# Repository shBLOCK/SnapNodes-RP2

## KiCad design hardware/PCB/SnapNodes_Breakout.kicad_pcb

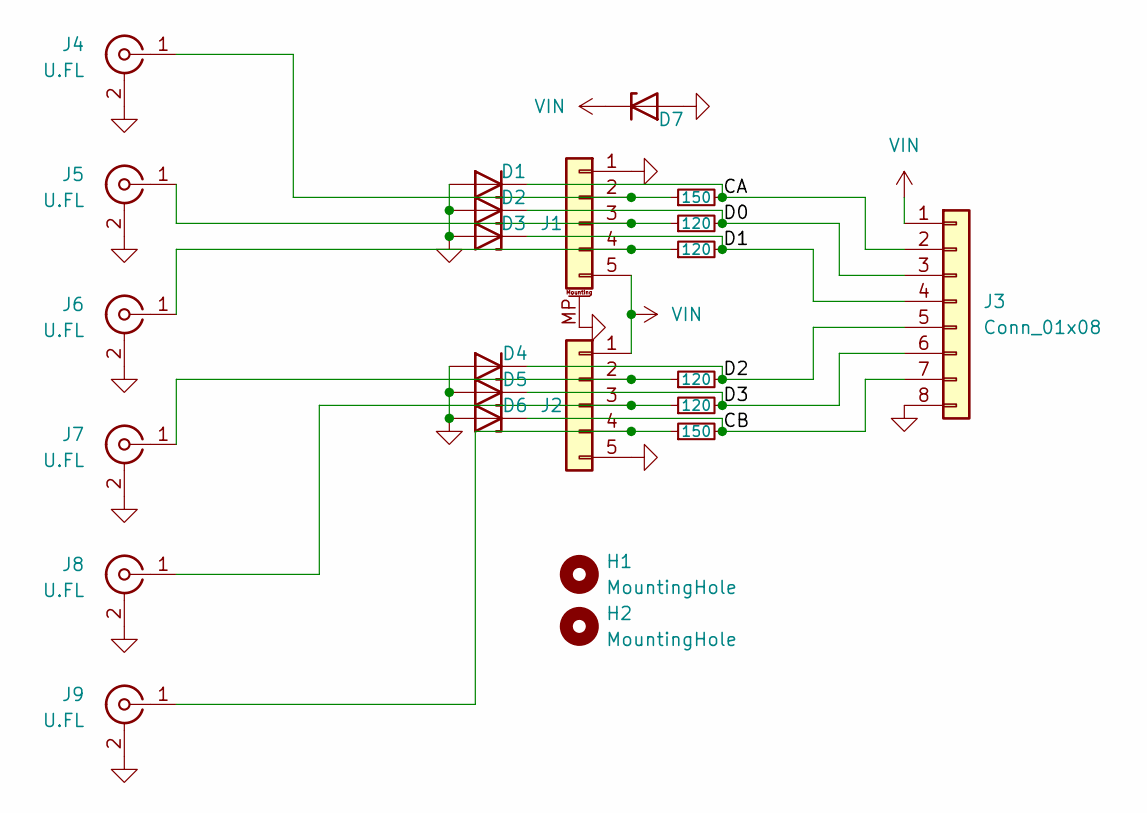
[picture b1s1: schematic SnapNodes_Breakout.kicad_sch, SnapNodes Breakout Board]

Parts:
D1, D2, D3, D4, D5, D6: PESD3V3S1BA; D_SOD-523; LCSC P/N C46550846
D7: PESD5V0S1BA; D_SOD-523; LCSC P/N C314264
H1, H2: MountingHole; MountingHole_2.2mm_M2
J1: P_Male; BC-15-5P380
J2: P_Female; BC-20-5PD160
J3: Conn_01x08; PinHeader_1x08_P2.54mm_Vertical
J4, J5, J6, J7, J8, J9: U.FL; U.FL_Hirose_U.FL-R-SMT-1_Vertical
R1, R6: 150; R_0402_1005Metric; LCSC P/N C25082
R2, R3, R4, R5: 120; R_0402_1005Metric; LCSC P/N C25079

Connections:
/CA: D1.1 (K), J3.2, R1.2
/CB: D6.1 (K), J3.7, R6.2
/D0: D2.1 (K), J3.3, R2.2
/D1: D3.1 (K), J3.4, R3.2
/D2: D4.1 (K), J3.5, R4.2
/D3: D5.1 (K), J3.6, R5.2
GND: D1.2 (A), D2.2 (A), D3.2 (A), D4.2 (A), D5.2 (A), D6.2 (A), D7.2 (A), J1.1, J1.MP (MountPin), J2.5, J3.8, J4.2 (Ext), J5.2 (Ext), J6.2 (Ext), J7.2 (Ext), J8.2 (Ext), J9.2 (Ext)
unnamed: J1.2, J4.1 (In), R1.1
unnamed: J1.3, J5.1 (In), R2.1
unnamed: J1.4, J6.1 (In), R3.1
unnamed: J2.2, J7.1 (In), R4.1
unnamed: J2.3, J8.1 (In), R5.1
unnamed: J2.4, J9.1 (In), R6.1
VIN: D7.1 (K), J1.5, J2.1, J3.1

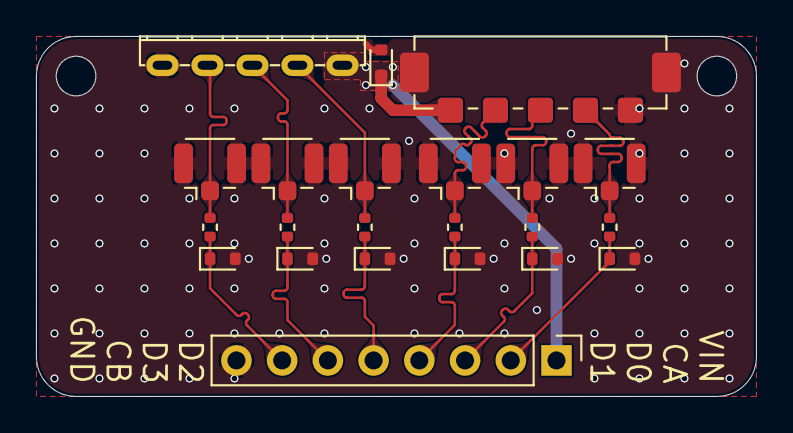
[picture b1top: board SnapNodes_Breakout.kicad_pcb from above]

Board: 4 copper layers, 40.0 x 20.0 mm, 24 parts (0 on the bottom side), 14 nets.

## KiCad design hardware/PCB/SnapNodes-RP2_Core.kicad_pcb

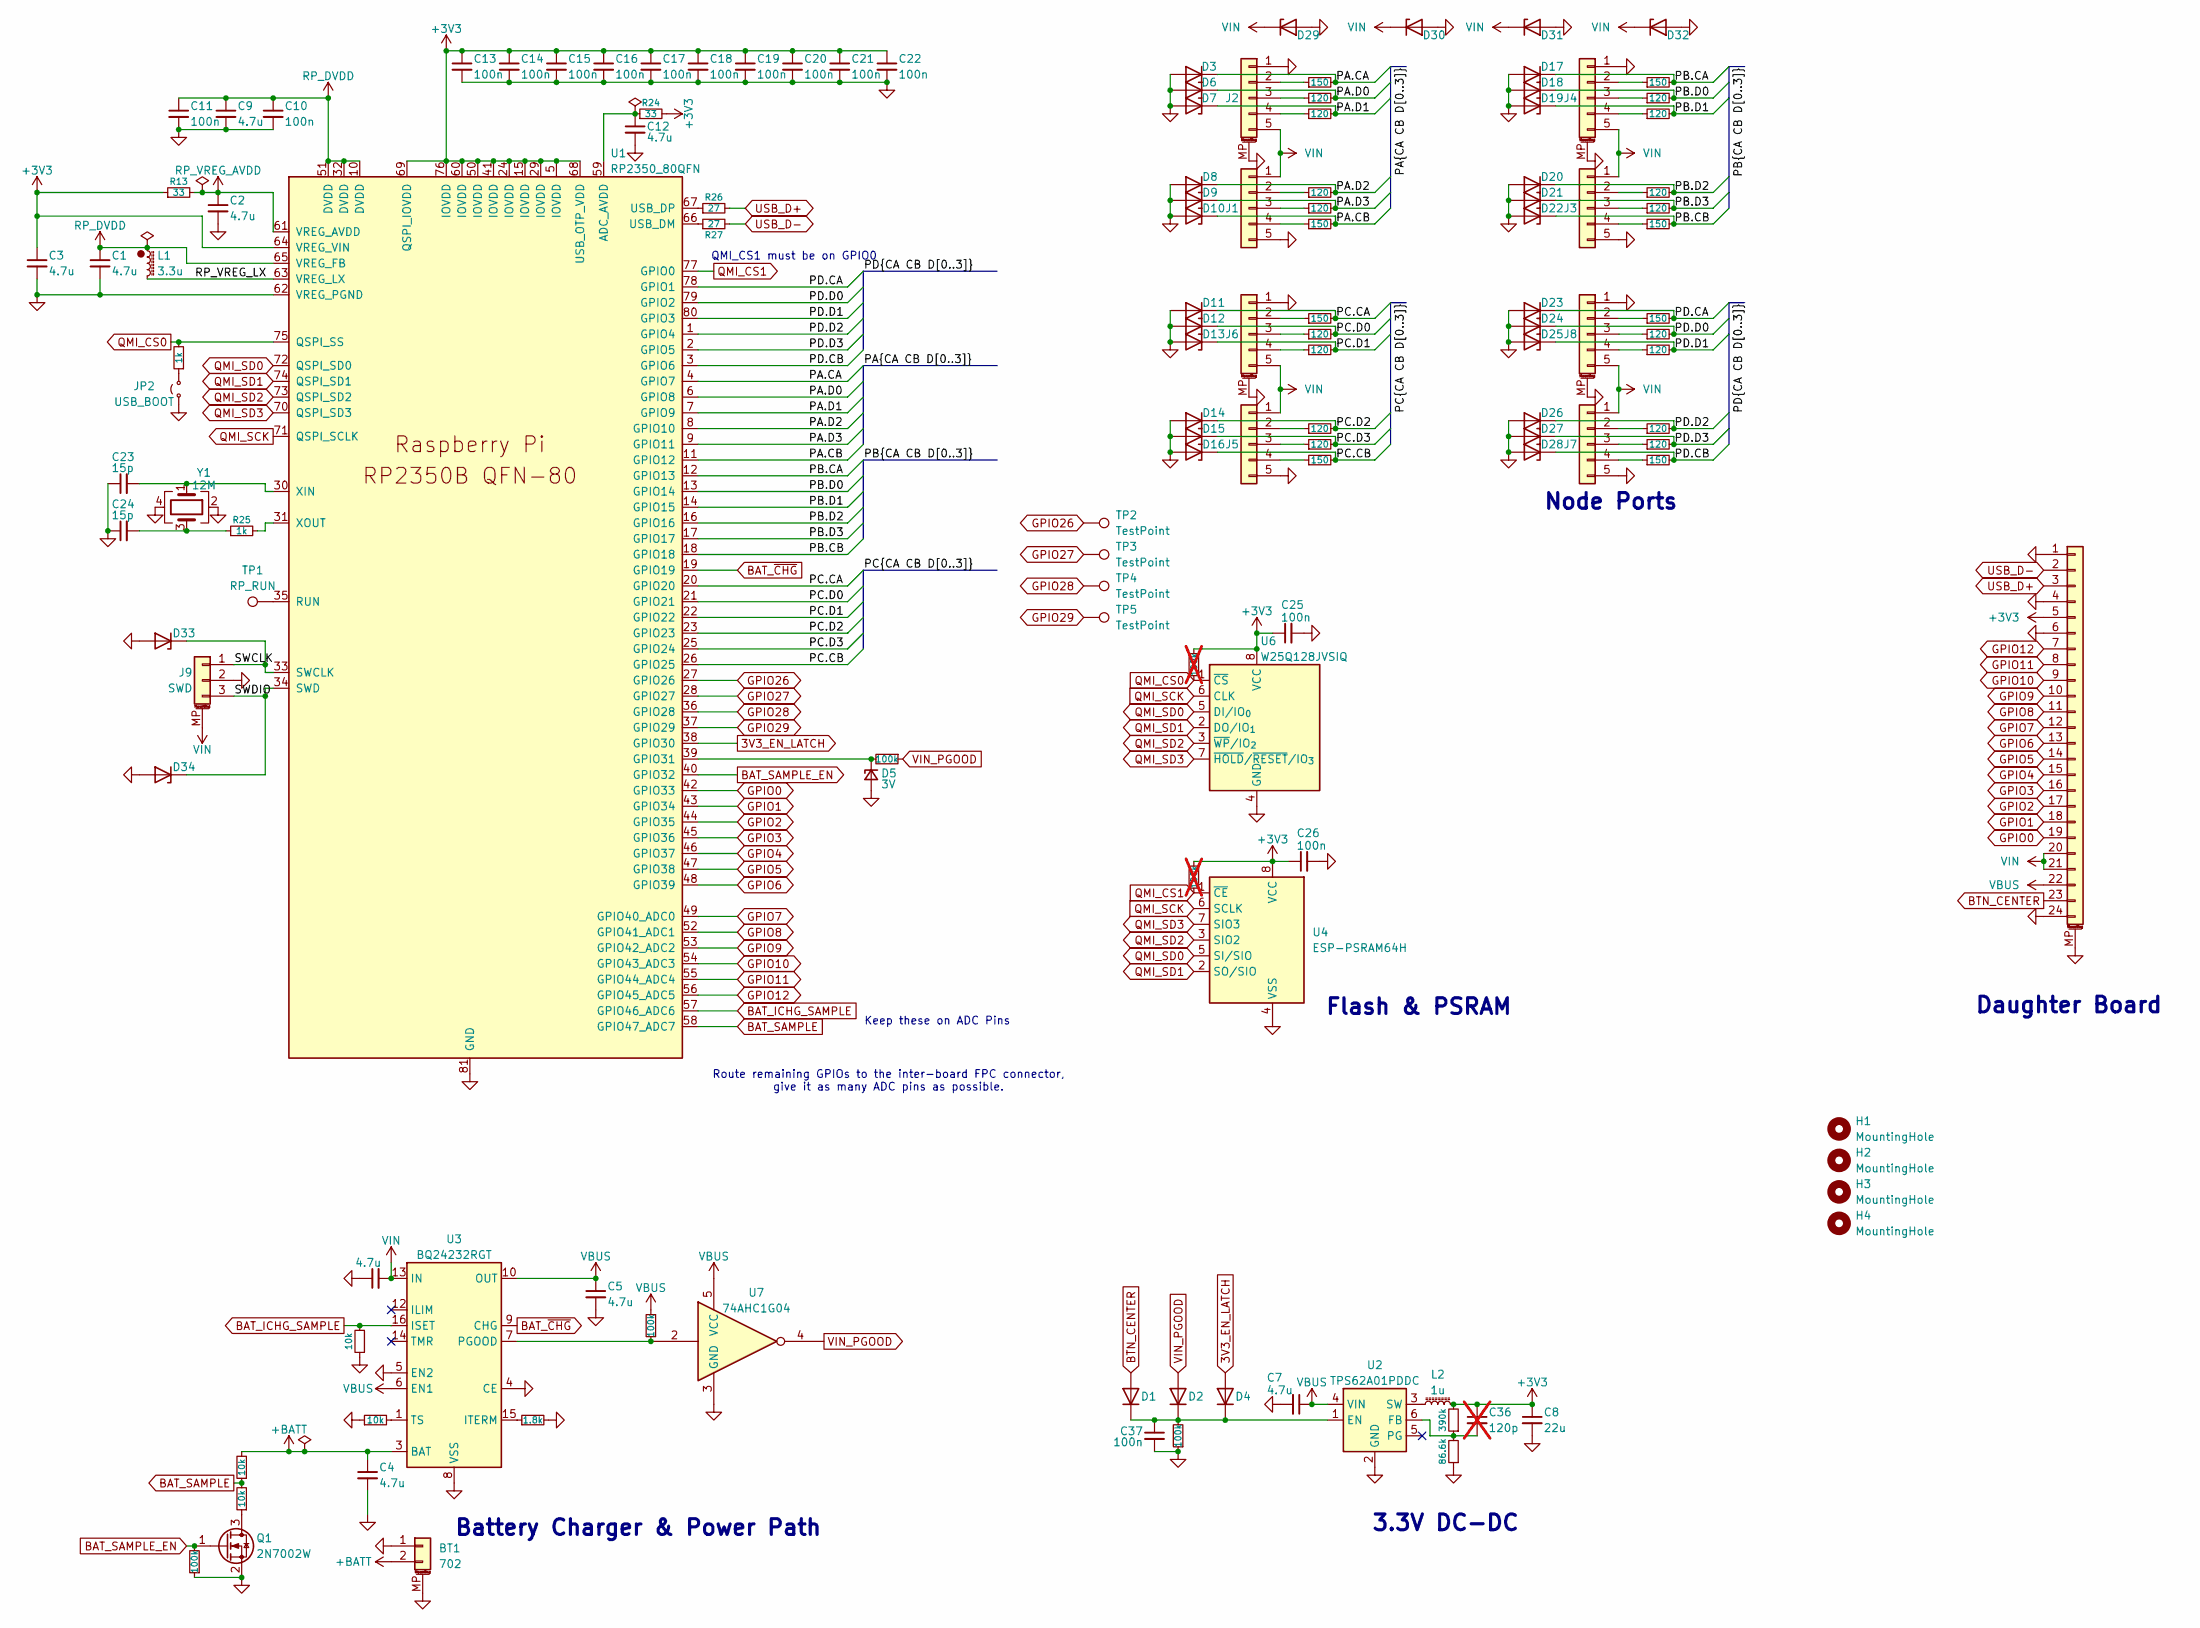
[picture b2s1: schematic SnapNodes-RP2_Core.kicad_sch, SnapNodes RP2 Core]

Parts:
BT1: 702; Molex_PicoBlade_53261-0271_1x02-1MP_P1.25mm_Horizontal; LCSC P/N C53477378
C1, C3: 4.7u; C_0402_1005Metric_small_pads; LCSC P/N C19666
C2, C4, C5, C6, C7, C9, C12: 4.7u; C_0402_1005Metric; LCSC P/N C19666
C8: 22u; C_0805_2012Metric; LCSC P/N C45783
C10, C11, C13, C14, C15, C16, C17, C18, C19, C20, C21, C22, C25, C26, C37: 100n; C_0402_1005Metric; LCSC P/N C1525
C23, C24: 15p; C_0402_1005Metric; LCSC P/N C1548
C36: 120p; C_0402_1005Metric; LCSC P/N C106996; not fitted
D1, D2, D4: 1N4148WT; D_SOD-523; LCSC P/N C7420320
D3, D6, D7, D8, D9, D10, D11, D12, D13, D14, D15, D16, D17, D18, D19, D20, D21, D22, D23, D24, D25, D26, D27, D28, D33, D34: PESD3V3S1BA; D_SOD-523; LCSC P/N C46550846
D5: 3V; D_SOD-523; LCSC P/N C2910134
D29, D30, D31, D32: PESD5V0S1BA; D_SOD-523; LCSC P/N C314264
H1, H2, H3, H4: MountingHole; MountingHole_2.2mm_M2
J1, J3, J5, J7: P_Female; BC-20-5PD160
J2, J4, J6, J8: P_Male; BC-15-5P380
J9: SWD; JST_SH_SM03B-SRSS-TB_1x03-1MP_P1.00mm_Horizontal; LCSC P/N C7430445
J20: Conn_01x24_MountingPin; FPC_Verticle_24pin_0.5mm; LCSC P/N C481246
JP2: USB_BOOT; PinHeader_1x02_P1.00mm_Vertical
L1: 3.3u; L_pol_2016; LCSC P/N C42411119
L2: 1u; L_Wuerth_MAPI-2010; LCSC P/N C7471163
Q1: 2N7002W; SOT-323_SC-70; LCSC P/N C7420322
R1, R4, R7, R10, R33, R37, R40, R43: 150; R_0402_1005Metric; LCSC P/N C25082
R2, R3, R5, R6, R8, R9, R11, R12, R31, R32, R35, R36, R38, R39, R41, R42: 120; R_0402_1005Metric; LCSC P/N C25079
R13, R24: 33; R_0402_1005Metric; LCSC P/N C25105
R14, R15, R17, R18: 10k; R_0402_1005Metric; LCSC P/N C25744
R16: 1.8k; R_0402_1005Metric; LCSC P/N C25871
R19, R22, R23, R34: 100k; R_0402_1005Metric; LCSC P/N C25741
R20: 86.6k; R_0402_1005Metric; LCSC P/N C19709
R21: 390k; R_0402_1005Metric; LCSC P/N C163467
R25, R30: 1k; R_0402_1005Metric; LCSC P/N C11702
R26, R27: 27; R_0402_1005Metric; LCSC P/N C25100
R28, R29: 100k; R_0402_1005Metric; LCSC P/N C25741; not fitted
TP1: RP_RUN; TestPoint_THTPad_D1.0mm_Drill0.5mm
TP2, TP3, TP4, TP5: TestPoint; TestPoint_Pad_D1.0mm
U1: RP2350_80QFN; RP2350-QFN-80-1EP_10x10_P0.4mm_EP3.4x3.4mm_ThermalVias; LCSC P/N C42415655
U2: TPS62A01PDDC; SOT-23-6; LCSC P/N C42267816
U3: BQ24232RGT; VQFN-16-1EP_3x3mm_P0.5mm_EP1.68x1.68mm_ThermalVias; LCSC P/N C528622
U4: ESP-PSRAM64H; SOIC-8_3.9x4.9mm_P1.27mm
U6: W25Q128JVSIQ; SOIC-8_5.3x5.3mm_P1.27mm; LCSC C113767
U7: 74AHC1G04; SOT-353_SC-70-5; LCSC P/N C52140422
Y1: 12M; Crystal_SMD_3225-4Pin_3.2x2.5mm; LCSC P/N C50430

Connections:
3V3_EN_LATCH: D4.2 (A), U1.38 (GPIO30)
+3V3: C3.1, C8.1, C13.1, C14.1, C15.1, C16.1, C17.1, C18.1, C19.1, C20.1, C21.1, C22.1, C25.1, C26.1, C36.1, J20.5, L2.2, R13.1, R21.2, R24.2, R28.2, R29.2, U1.5 (IOVDD), U1.15 (IOVDD), U1.24 (IOVDD), U1.29 (IOVDD), U1.41 (IOVDD), U1.50 (IOVDD), U1.60 (IOVDD), U1.64 (VREG_VIN), U1.68 (USB_OTP_VDD), U1.69 (QSPI_IOVDD), U1.76 (IOVDD), U4.8 (VCC), U6.8 (VCC)
+BATT: BT1.2, C4.1, R18.2, U3.2 (BAT), U3.3 (BAT)
/PA.CA: D3.1 (K), R1.2, U1.4 (GPIO7)
/PA.CB: D10.1 (K), R33.2, U1.11 (GPIO12)
/PA.D0: D6.1 (K), R31.2, U1.6 (GPIO8)
/PA.D1: D7.1 (K), R2.2, U1.7 (GPIO9)
/PA.D2: D8.1 (K), R32.2, U1.8 (GPIO10)
/PA.D3: D9.1 (K), R3.2, U1.9 (GPIO11)
/PB.CA: D17.1 (K), R4.2, U1.12 (GPIO13)
/PB.CB: D22.1 (K), R40.2, U1.18 (GPIO18)
/PB.D0: D18.1 (K), R38.2, U1.13 (GPIO14)
/PB.D1: D19.1 (K), R5.2, U1.14 (GPIO15)
/PB.D2: D20.1 (K), R39.2, U1.16 (GPIO16)
/PB.D3: D21.1 (K), R6.2, U1.17 (GPIO17)
/PC.CA: D11.1 (K), R7.2, U1.20 (GPIO20)
/PC.CB: D16.1 (K), R37.2, U1.26 (GPIO25)
/PC.D0: D12.1 (K), R35.2, U1.21 (GPIO21)
/PC.D1: D13.1 (K), R8.2, U1.22 (GPIO22)
/PC.D2: D14.1 (K), R36.2, U1.23 (GPIO23)
/PC.D3: D15.1 (K), R9.2, U1.25 (GPIO24)
/PD.CA: D23.1 (K), R10.2, U1.78 (GPIO1)
/PD.CB: D28.1 (K), R43.2, U1.3 (GPIO6)
/PD.D0: D24.1 (K), R41.2, U1.79 (GPIO2)
/PD.D1: D25.1 (K), R11.2, U1.80 (GPIO3)
/PD.D2: D26.1 (K), R42.2, U1.1 (GPIO4)
/PD.D3: D27.1 (K), R12.2, U1.2 (GPIO5)
/RP_VREG_LX: L1.2, U1.63 (VREG_LX)
/SWCLK: D33.1 (K), J9.1, U1.33 (SWCLK)
/SWDIO: D34.1 (K), J9.3, U1.34 (SWD)
BAT_ICHG_SAMPLE: R15.2, U1.57 (GPIO46_ADC6), U3.16 (ISET)
BAT_SAMPLE: R17.2, R18.1, U1.58 (GPIO47_ADC7)
BAT_SAMPLE_EN: Q1.1 (G), R19.2, U1.40 (GPIO32)
BAT_~CHG: U1.19 (GPIO19), U3.9 (CHG)
BTN_CENTER: D1.2 (A), J20.23
GND: BT1.1, BT1.MP (MountPin), C1.2, C2.2, C3.2, C4.2, C5.2, C6.1, C7.2, C8.2, C9.2, C10.2, C11.2, C12.2, C13.2, C14.2, C15.2, C16.2, C17.2, C18.2, C19.2, C20.2, C21.2, C22.2, C23.1, C24.1, C25.2, C26.2, C37.2, D3.2 (A), D5.2 (A), D6.2 (A), D7.2 (A), D8.2 (A), D9.2 (A), D10.2 (A), D11.2 (A), D12.2 (A), D13.2 (A), D14.2 (A), D15.2 (A), D16.2 (A), D17.2 (A), D18.2 (A), D19.2 (A), D20.2 (A), D21.2 (A), D22.2 (A), D23.2 (A), D24.2 (A), D25.2 (A), D26.2 (A), D27.2 (A), D28.2 (A), D29.2 (A), D30.2 (A), D31.2 (A), D32.2 (A), D33.2 (A), D34.2 (A), J1.5, J2.1, J2.MP (MountPin), J3.5, J4.1, J4.MP (MountPin), J5.5, J6.1, J6.MP (MountPin), J7.5, J8.1, J8.MP (MountPin), J9.2, J9.MP (MountPin), J20.1, J20.4, J20.6, J20.24, J20.MP (MountPin), JP2.1 (A), Q1.2 (S), R14.1, R15.1, R16.2, R19.1, R20.1, R34.1, U1.62 (VREG_PGND), U1.81 (GND), U2.2 (GND), U3.4 (CE), U3.5 (EN2), U3.8 (VSS), U3.17 (VSS), U4.4 (VSS), U6.4 (GND), U7.3 (GND), Y1.2, Y1.4
GPIO0: J20.19, U1.42 (GPIO33)
GPIO1: J20.18, U1.43 (GPIO34)
GPIO2: J20.17, U1.44 (GPIO35)
GPIO3: J20.16, U1.45 (GPIO36)
GPIO4: J20.15, U1.46 (GPIO37)
GPIO5: J20.14, U1.47 (GPIO38)
GPIO6: J20.13, U1.48 (GPIO39)
GPIO7: J20.12, U1.49 (GPIO40_ADC0)
GPIO8: J20.11, U1.52 (GPIO41_ADC1)
GPIO9: J20.10, U1.53 (GPIO42_ADC2)
GPIO10: J20.9, U1.54 (GPIO43_ADC3)
GPIO11: J20.8, U1.55 (GPIO44_ADC4)
GPIO12: J20.7, U1.56 (GPIO45_ADC5)
GPIO26: TP2.1 (1_1), U1.27 (GPIO26)
GPIO27: TP3.1 (1_1), U1.28 (GPIO27)
GPIO28: TP4.1 (1_1), U1.36 (GPIO28)
GPIO29: TP5.1 (1_1), U1.37 (GPIO29)
unnamed: C24.2, R25.1, Y1.3
unnamed: C37.1, D1.1 (K), D2.1 (K), D4.1 (K), R34.2, U2.1 (EN)
unnamed: D5.1 (K), R23.2, U1.39 (GPIO31)
unnamed: J1.2, R32.1
unnamed: J1.3, R3.1
unnamed: J1.4, R33.1
unnamed: J2.2, R1.1
unnamed: J2.3, R31.1
unnamed: J2.4, R2.1
unnamed: J3.2, R39.1
unnamed: J3.3, R6.1
unnamed: J3.4, R40.1
unnamed: J4.2, R4.1
unnamed: J4.3, R38.1
unnamed: J4.4, R5.1
unnamed: J5.2, R36.1
unnamed: J5.3, R9.1
unnamed: J5.4, R37.1
unnamed: J6.2, R7.1
unnamed: J6.3, R35.1
unnamed: J6.4, R8.1
unnamed: J7.2, R42.1
unnamed: J7.3, R12.1
unnamed: J7.4, R43.1
unnamed: J8.2, R10.1
unnamed: J8.3, R41.1
unnamed: J8.4, R11.1
unnamed: JP2.2 (B), R30.1
unnamed: Q1.3 (D), R17.1
unnamed: C12.1, R24.1, U1.59 (ADC_AVDD)
unnamed: TP1.1 (1_1), U1.35 (RUN)
unnamed: R27.1, U1.66 (USB_DM)
unnamed: R26.1, U1.67 (USB_DP)
unnamed: C23.2, U1.30 (XIN), Y1.1
unnamed: R25.2, U1.31 (XOUT)
unnamed: C36.2, R20.2, R21.1, U2.6 (FB)
unnamed: L2.1, U2.3 (SW)
unnamed: R16.1, U3.15 (ITERM)
unnamed: R22.2, U3.7 (PGOOD), U7.2
unnamed: R14.2, U3.1 (TS)
QMI_CS0: R28.1, R30.2, U1.75 (QSPI_SS), U6.1 (~CS)
QMI_CS1: R29.1, U1.77 (GPIO0), U4.1 (~CE)
QMI_SCK: U1.71 (QSPI_SCLK), U4.6 (SCLK), U6.6 (CLK)
QMI_SD0: U1.72 (QSPI_SD0), U4.5 (SI/SIO), U6.5 (DI/IO_{0})
QMI_SD1: U1.74 (QSPI_SD1), U4.2 (SO/SIO), U6.2 (DO/IO_{1})
QMI_SD2: U1.73 (QSPI_SD2), U4.3 (SIO2), U6.3 (~WP/IO_{2})
QMI_SD3: U1.70 (QSPI_SD3), U4.7 (SIO3), U6.7 (~HOLD/~RESET/IO_{3})
RP_DVDD: C1.1, C9.1, C10.1, C11.1, L1.1, U1.10 (DVDD), U1.32 (DVDD), U1.51 (DVDD), U1.65 (VREG_FB)
RP_VREG_AVDD: C2.1, R13.2, U1.61 (VREG_AVDD)
USB_D+: J20.3, R26.2
USB_D-: J20.2, R27.2
VBUS: C5.1, C7.1, J20.22, R22.1, U2.4 (VIN), U3.6 (EN1), U3.10 (OUT), U3.11 (OUT), U7.5 (VCC)
VIN: C6.2, D29.1 (K), D30.1 (K), D31.1 (K), D32.1 (K), J1.1, J2.5, J3.1, J4.5, J5.1, J6.5, J7.1, J8.5, J9.MP (MountPin), J20.20, J20.21, U3.13 (IN)
VIN_PGOOD: D2.2 (A), R23.1, U7.4

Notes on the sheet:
Battery Charger & Power Path
Route remaining GPIOs to the inter-board FPC connector, give it as many ADC pins as possible.
QMI_CS1 must be on GPIO0
Node Ports
Keep these on ADC Pins
Daughter Board
3.3V DC-DC
Flash & PSRAM

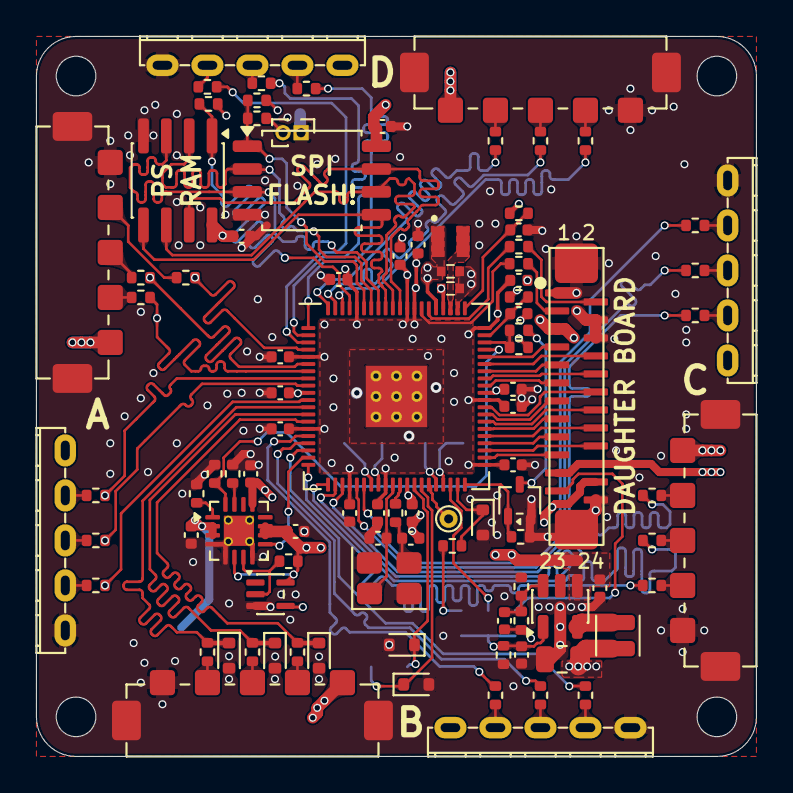
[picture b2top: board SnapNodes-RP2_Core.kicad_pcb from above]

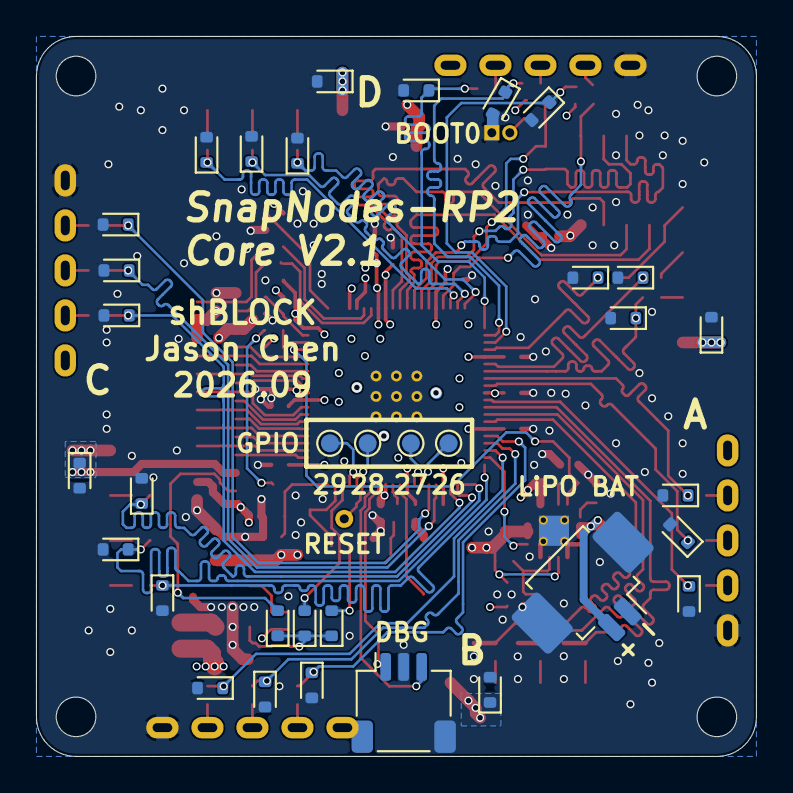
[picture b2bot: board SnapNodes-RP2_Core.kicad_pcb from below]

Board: 4 copper layers, 40.0 x 40.0 mm, 136 parts (34 on the bottom side), 107 nets.

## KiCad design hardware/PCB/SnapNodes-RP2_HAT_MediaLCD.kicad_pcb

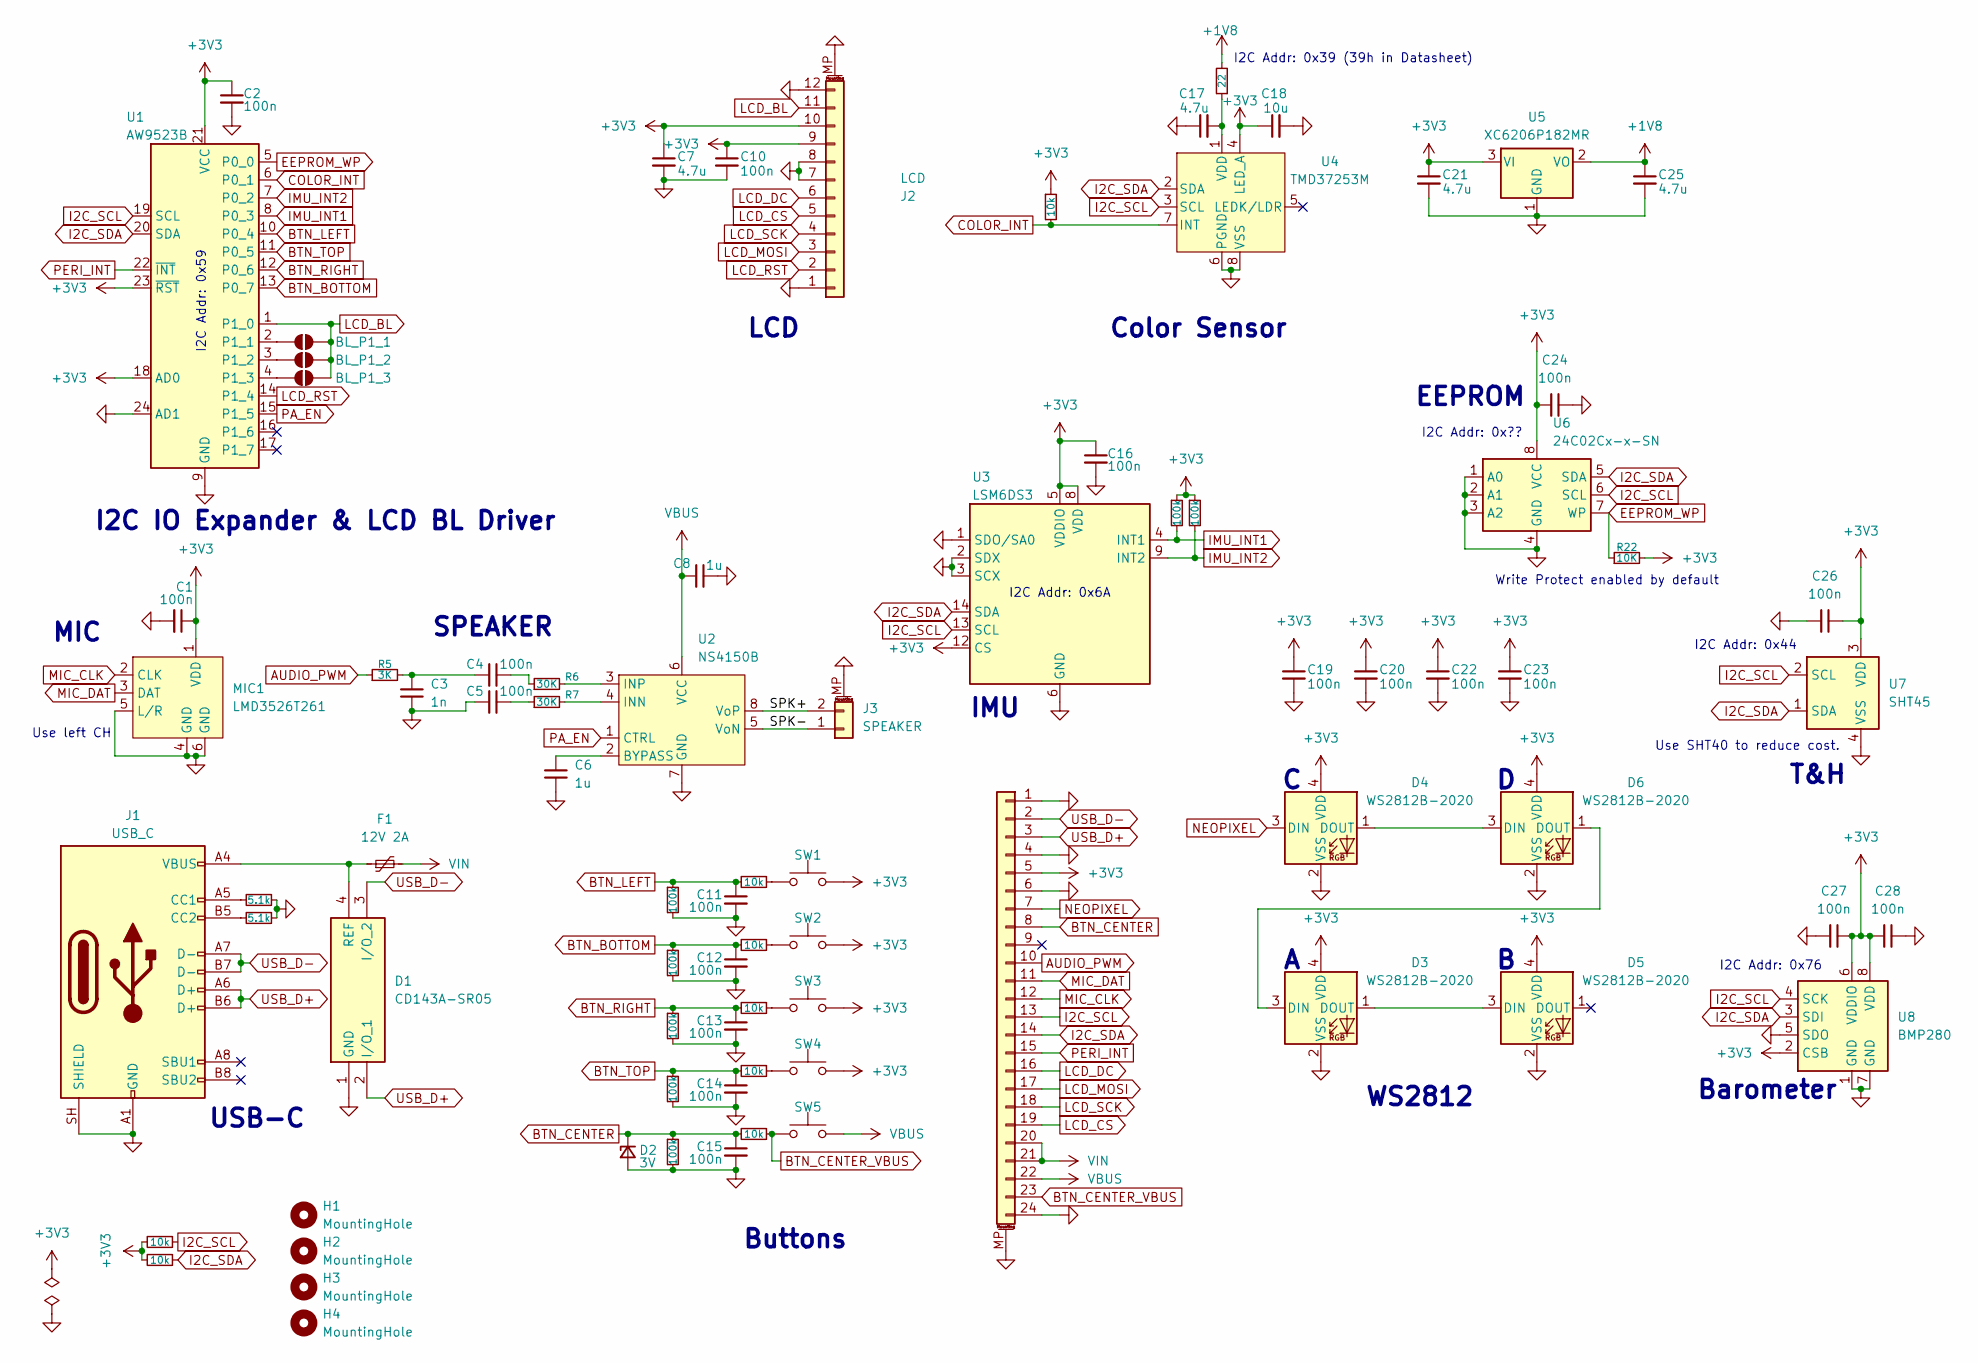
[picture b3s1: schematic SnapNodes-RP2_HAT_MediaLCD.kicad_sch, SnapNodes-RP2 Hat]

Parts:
C1, C2, C4, C5, C10, C11, C12, C13, C14, C15, C16, C19, C20, C22, C23, C24, C26, C27, C28: 100n; C_0603_1608Metric; LCSC P/N C14663
C3: 1n; C_0603_1608Metric; LCSC P/N C1588
C6, C8: 1u; C_0603_1608Metric; LCSC P/N C15849
C7, C17, C21, C25: 4.7u; C_0603_1608Metric; LCSC P/N C19666
C18: 10u; C_0603_1608Metric; LCSC P/N C19702
D1: CD143A-SR05; SOT-143; Manufacturer_Part_Number CD143A-SR05; Mouser Part Number 652-CD143A-SR05
D2: 3V; D_SOD-523; LCSC P/N C2910134
D3, D4, D5, D6: WS2812B-2020; LED_WS2812B-2020_PLCC4_2.0x2.0mm; LCSC P/N C52917434
F1: 12V 2A; Fuse_0805_2012Metric; LCSC P/N C48783161
H1, H2, H3, H4: MountingHole; MountingHole_2.2mm_M2
J1: USB_C; USB_C_Receptacle_GCT_USB4105-xx-A_16P_TopMnt_Horizontal; LCSC P/N C2765186
J2: LCD; TE_1-1734839-2_1x12-1MP_P0.5mm_Horizontal; LCSC P/N C49274051
J3: SPEAKER; Molex_PicoBlade_53261-0271_1x02-1MP_P1.25mm_Horizontal; LCSC P/N C53477378
J4: Conn_01x24_MountingPin; FPC_Verticle_24pin_0.5mm; LCSC P/N C481246
JP1: BL_P1_1; SolderJumper-2_P1.3mm_Open_RoundedPad1.0x1.5mm
JP2: BL_P1_2; SolderJumper-2_P1.3mm_Open_RoundedPad1.0x1.5mm
JP3: BL_P1_3; SolderJumper-2_P1.3mm_Open_RoundedPad1.0x1.5mm
MIC1: LMD3526T261; MIC-SMD_6P-L3.5-W2.7-P0.884-TR; LCSC P/N C49230436
R1, R2, R13, R14, R15, R16, R17, R18: 10k; R_0603_1608Metric; LCSC P/N C25804
R3, R4: 5.1k; R_0603_1608Metric; LCSC P/N C23186
R5: 3K; R_0603_1608Metric; LCSC P/N C4211
R6, R7: 30K; R_0603_1608Metric; LCSC P/N C22984
R8, R9, R10, R11, R12, R19, R20: 100k; R_0603_1608Metric; LCSC P/N C25803
R21: 22; R_0603_1608Metric; LCSC P/N C23345
R22: 10K; R_0603_1608Metric; LCSC P/N C25804
SW1: Left; SW_SPST_PTS647_Sx38
SW2: Bottom; SW_SPST_PTS647_Sx38
SW3: Right; SW_SPST_PTS647_Sx38
SW4: Top; SW_SPST_PTS647_Sx38
SW5: Center; SW_SPST_PTS647_Sx38
U1: AW9523B; QFN-24-1EP_4x4mm_P0.5mm_EP2.7x2.7mm_ThermalVias; LCSC P/N C148077
U2: NS4150B; MSOP-8_3x3mm_P0.65mm; LCSC P/N C189961
U3: LSM6DS3; LGA-14_3x2.5mm_P0.5mm_LayoutBorder3x4y; LCSC P/N C95230
U4: TMD37253M; LGA8_TMD37253_OSM; LCSC P/N C2153068
U5: XC6206P182MR; SOT-23-3; LCSC P/N C347373
U6: 24C02Cx-x-SN; SOIC-8_3.9x4.9mm_P1.27mm
U7: SHT45; Sensirion_DFN-4_1.5x1.5mm_P0.8mm_SHT4x_NoCentralPad
U8: BMP280; Bosch_LGA-8_2x2.5mm_P0.65mm_ClockwisePinNumbering

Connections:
+1V8: C25.1, R21.2, U5.2 (VO)
+3V3: C1.1, C2.1, C7.1, C10.1, C16.1, C18.1, C19.1, C20.1, C21.1, C22.1, C23.1, C24.1, C26.2, C27.2, C28.1, D3.4 (VDD), D4.4 (VDD), D5.4 (VDD), D6.4 (VDD), J2.9, J2.10, J4.5, MIC1.1 (VDD), R1.2, R2.2, R18.1, R19.1, R20.1, R22.2, SW1.2, SW2.2, SW3.2, SW4.2, U1.18 (AD0), U1.21 (VCC), U1.23 (~RST), U3.5 (VDDIO), U3.8 (VDD), U3.12 (CS), U4.4 (LED_A), U5.3 (VI), U6.8 (VCC), U7.3 (VDD), U8.2 (CSB), U8.6 (VDDIO), U8.8 (VDD)
/SPK+: J3.2, U2.8 (VoP)
/SPK-: J3.1, U2.5 (VoN)
AUDIO_PWM: J4.10, R5.1
BTN_BOTTOM: C12.1, R9.1, R14.2, U1.13 (P0_7)
BTN_CENTER: C15.1, D2.1 (K), J4.8, R12.1, R17.2
BTN_CENTER_VBUS: J4.23, R17.1, SW5.1
BTN_LEFT: C11.1, R8.1, R13.2, U1.10 (P0_4)
BTN_RIGHT: C13.1, R10.1, R15.2, U1.12 (P0_6)
BTN_TOP: C14.1, R11.1, R16.2, U1.11 (P0_5)
COLOR_INT: R18.2, U1.6 (P0_1), U4.7 (INT)
EEPROM_WP: R22.1, U1.5 (P0_0), U6.7 (WP)
GND: C1.2, C2.2, C3.1, C5.1, C6.1, C7.2, C8.1, C10.2, C11.2, C12.2, C13.2, C14.2, C15.2, C16.2, C17.1, C18.2, C19.2, C20.2, C21.2, C22.2, C23.2, C24.2, C25.2, C26.1, C27.1, C28.2, D1.1 (GND), D2.2 (A), D3.2 (VSS), D4.2 (VSS), D5.2 (VSS), D6.2 (VSS), J1.A1 (GND), J1.A12 (GND), J1.B1 (GND), J1.B12 (GND), J1.SH (SHIELD), J2.1, J2.7, J2.8, J2.12, J2.MP (MountPin), J3.MP (MountPin), J4.1, J4.4, J4.6, J4.24, J4.MP (MountPin), MIC1.4 (GND), MIC1.5 (L/R), MIC1.6 (GND), R3.1, R4.1, R8.2, R9.2, R10.2, R11.2, R12.2, U1.9 (GND), U1.24 (AD1), U1.25 (GND), U2.7 (GND), U3.1 (SDO/SA0), U3.2 (SDX), U3.3 (SCX), U3.6 (GND), U3.7 (GND), U4.6 (PGND), U4.8 (VSS), U5.1 (GND), U6.1 (A0), U6.2 (A1), U6.3 (A2), U6.4 (GND), U7.4 (VSS), U8.1 (GND), U8.5 (SDO), U8.7 (GND)
I2C_SCL: J4.13, R1.1, U1.19 (SCL), U3.13 (SCL), U4.3 (SCL), U6.6 (SCL), U7.2 (SCL), U8.4 (SCK)
I2C_SDA: J4.14, R2.1, U1.20 (SDA), U3.14 (SDA), U4.2 (SDA), U6.5 (SDA), U7.1 (SDA), U8.3 (SDI)
IMU_INT1: R19.2, U1.8 (P0_3), U3.4 (INT1)
IMU_INT2: R20.2, U1.7 (P0_2), U3.9 (INT2)
LCD_BL: J2.11, JP1.2 (B), JP2.2 (B), JP3.2 (B), U1.1 (P1_0)
LCD_CS: J2.5, J4.19
LCD_DC: J2.6, J4.16
LCD_MOSI: J2.3, J4.17
LCD_RST: J2.2, U1.14 (P1_4)
LCD_SCK: J2.4, J4.18
MIC_CLK: J4.12, MIC1.2 (CLK)
MIC_DAT: J4.11, MIC1.3 (DAT)
NEOPIXEL: D4.3 (DIN), J4.7
unnamed: C3.2, C4.1, R5.2
unnamed: C4.2, R6.1
unnamed: C5.2, R7.1
unnamed: D1.4 (REF), F1.1, J1.A4 (VBUS), J1.A9 (VBUS), J1.B4 (VBUS), J1.B9 (VBUS)
unnamed: D3.3 (DIN), D6.1 (DOUT)
unnamed: D3.1 (DOUT), D5.3 (DIN)
unnamed: D4.1 (DOUT), D6.3 (DIN)
unnamed: J1.A5 (CC1), R3.2
unnamed: J1.B5 (CC2), R4.2
unnamed: JP1.1 (A), U1.2 (P1_1)
unnamed: JP2.1 (A), U1.3 (P1_2)
unnamed: JP3.1 (A), U1.4 (P1_3)
unnamed: R13.1, SW1.1
unnamed: R14.1, SW2.1
unnamed: R15.1, SW3.1
unnamed: R16.1, SW4.1
unnamed: C6.2, U2.2 (BYPASS)
unnamed: R7.2, U2.4 (INN)
unnamed: R6.2, U2.3 (INP)
unnamed: C17.2, R21.1, U4.1 (VDD)
PA_EN: U1.15 (P1_5), U2.1 (CTRL)
PERI_INT: J4.15, U1.22 (~INT)
USB_D+: D1.2 (I/O_1), J1.A6 (D+), J1.B6 (D+), J4.3
USB_D-: D1.3 (I/O_2), J1.A7 (D-), J1.B7 (D-), J4.2
VBUS: C8.2, J4.22, SW5.2, U2.6 (VCC)
VIN: F1.2, J4.20, J4.21

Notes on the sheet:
I2C IO Expander & LCD BL Driver
Barometer
SPEAKER
Color Sensor
USB-C
EEPROM
I2C Addr: 0x76
WS2812
Use left CH
MIC
Buttons
LCD
I2C Addr: 0x44
I2C Addr: 0x59
I2C Addr: 0x39 (39h in Datasheet)
I2C Addr: 0x6A
IMU
I2C Addr: 0x??
Use SHT40 to reduce cost.
Write Protect enabled by default
T&H

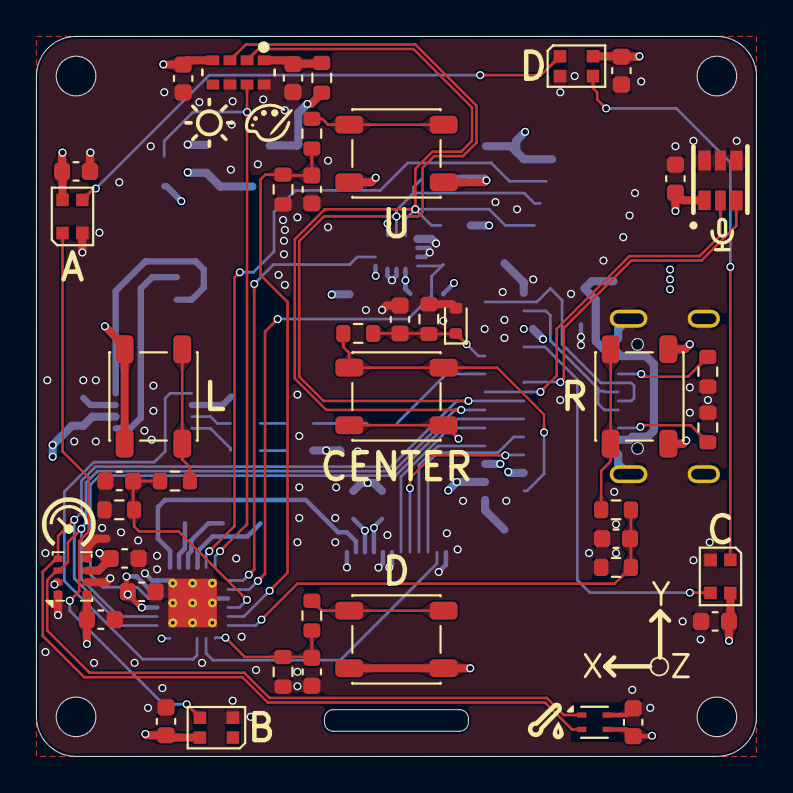
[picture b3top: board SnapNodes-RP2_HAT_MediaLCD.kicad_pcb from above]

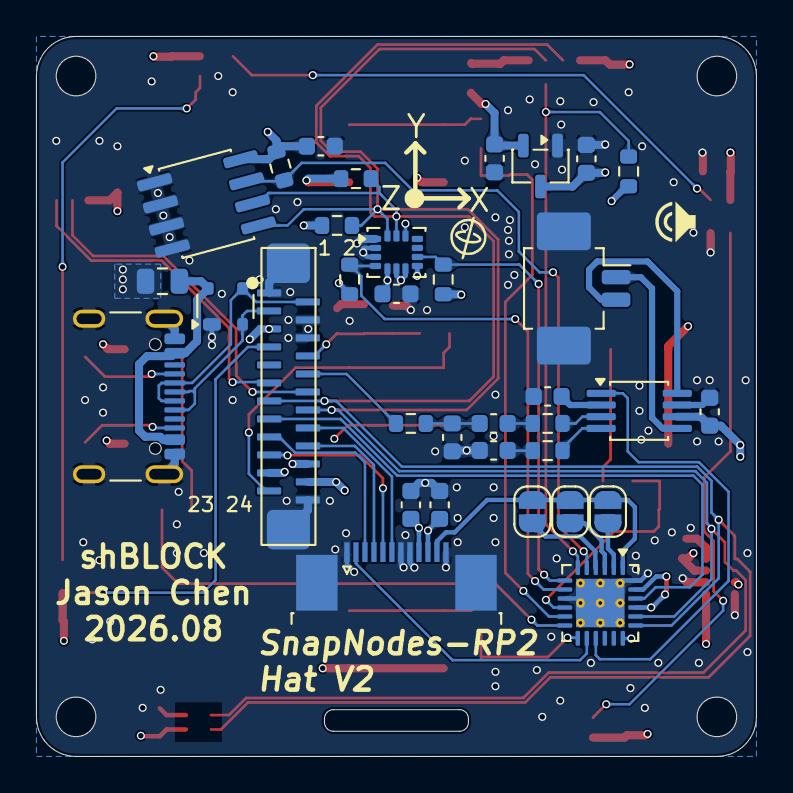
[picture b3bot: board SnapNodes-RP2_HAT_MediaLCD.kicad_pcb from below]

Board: 4 copper layers, 40.0 x 40.0 mm, 81 parts (34 on the bottom side), 53 nets.

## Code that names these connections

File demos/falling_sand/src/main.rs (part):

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    // {
    //     let mut cfg = embassy_rp::psram::Config::aps6404l();
    //     cfg.clock_hz = SYS_CLOCK_HZ;
    //     embassy_rp::psram::Psram::new(embassy_rp::qmi_cs1::QmiCs1::new(ps.QMI_CS1, ps.PIN_0), cfg)
    //         .expect("Failed to initialize PSRAM");
    //
    //     unsafe extern "C" {
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            type Error = core::convert::Infallible;
        }

        let mut lcd_cs = Output::new(ps.PIN_33, embassy_rp::gpio::Level::High);
        let lcd_clk = ps.PIN_34;
        let lcd_mosi = ps.PIN_35;
        let lcd_dc = Output::new(ps.PIN_36, embassy_rp::gpio::Level::Low);
        let mut lcd_spi_cfg = embassy_rp::spi::Config::default();
        lcd_spi_cfg.frequency = 64_000_000;
        lcd_spi_cfg.phase = embassy_rp::spi::Phase::CaptureOnSecondTransition;
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
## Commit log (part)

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2026-01-04 Falling sand demo works!
2026-01-17 Falling sand demo wip
2026-01-17 Move PCB files from TileGlobeMC to this repo. Revision WIP
